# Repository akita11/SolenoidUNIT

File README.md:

# SolenoidUNIT

ソレノイドやDCモータなどの負荷を、Grove端子から最大2個まで制御できます。負荷と電源の接続コネクタの違いで2種類あります。

## SolenoidUNIT

オレンジ色のコネクタ(VH3.96-4p)に、負荷用の電源と負荷を接続します。M5Stackの[BAVGソケット](https://www.switch-science.com/products/7234)を使うと、電源は2.1mmプラグ、負荷はスプリング端子で接続できて便利です。

負荷の電源はオレンジ色のVH3.96コネクタ、またはGrove端子のVDDから選択できます。Grove端子のVDDへの電源供給能力が不足する場合は[TypeC2Grove UNIT](https://www.switch-science.com/products/8453)等を使用してください。

基板形状が「[M5Stack用VH3.96-4ピンユニット[U020]](https://www.switch-science.com/products/4055)」と同一のため、そのケースを使うことができます。

### 使い方

ソレノイドとの接続は、電源供給方法に応じて以下の2通りがあります。制御方法は後述します。

#### ACアダプタ等から供給する場合

ソレノイドの定格電圧が12V等の5Vよりも高い電圧の場合は、ACアダプタ等をオレンジ色コネクタのVS-G間、ソレノイドをA+とA-Bの間に接続します。（M5Stackの[BAVGソケット](https://www.switch-science.com/products/7234)を使うと、電源は2.1mmプラグ、負荷はスプリング端子で接続できて便利です）

#### Grove端子から供給する場合

一般のソレノイドは5Vでは駆動できませんが、5Vで駆動する場合は、電源をGrove端子から供給することができます。
裏面のJP1の、中央-VS(上側)の端子がつながっていますので、カッター等でカットし、中央と反対側の"Grove5V"側を、ハンダを盛るなどしてショートします。これによって、負荷への電源がGrove側の+5Vから供給されます。
ただし、一般にソレノイドは消費電流が多く、マイコン側の+5V電源の供給能力が不足する場合がほとんどです。そのような場合は、[TypeC2Grove UNIT](https://www.switch-science.com/products/8453)を使用して、負荷側の電源をUSB Type-C端子から供給することができます。別途USB-CコネクタのACアダプタ等を接続してください。

#### 2個のソレノイドを制御する場合

必要に応じて、2個のソレノイドを制御することができます。ただし接続がやや複雑ですので、ご注意ください。

- JP2 : VH3.96コネクタの2番ピンの割り当て。「負荷Aのプラス側」（デフォルト）または「負荷Bのマイナス側」。
  - 「負荷Aのプラス側」（デフォルト）の場合（下図(a)）：負荷Aを1番ピン（マイナス側）と2番ピン（プラス側）に接続。負荷は1個のみ(Groveの1番ピンで制御）
  - 「負荷Bのマイナス側の場合」（下図(b)）：負荷A, Bのプラス側はVDD（3番ピン）に接続し、負荷A, Bのマイナス側をそれぞれ1番ピンと2番ピンに接続。負荷は2個（Groveの1番ピン（負荷A）と2番ピン（負荷B）で制御）

## Solenoid5V_UNIT

[タカハの5Vソレノイド](https://www.takaha.co.jp/co/ss/)を接続して制御できます。

基板形状が「[M5Stack用VH3.96-4ピンユニット[U020]](https://www.switch-science.com/products/4055)」と同一のため、そのケースを使うことができます。

2段USBコネクタの上側がソレノイドA（Groveの1番ピンで制御）、下側がソレノイドB（Grovの2番ピンで制御）です。

マイコン（M5Stack等）との接続は以下のように行います。

ただしソレノイドは通電時の消費電流が大きいため、マイコン側の電源供給能力が不足する場合があります。その場合は、[TypeC2Grove UNIT](https://www.switch-science.com/products/8453)を使用して以下のように接続してください。負荷側の電源はUSB Type-C端子から供給することができます。別途USB-CコネクタのACアダプタ等を接続してください。

## マイコン(M5Stack等)からの制御

ソレノイドのの制御は、Grove端子の2本の信号（A/B/VDD/GNDの順）で行います。AまたはBに"1"を与えると負荷がONとなり、"0"でOFFとなります。SolenoidUnitの標準接続（ソレノイド1個）ではA端子のみを使います。

UIFlowでの[使用例](Solenoid5V_test.m5f)（以下）を参考にしてください。（Core2のPortAに接続した場合。A=GPIO32、B=GPIO33）

## Author

Junichi Akita (akita@ifdl.jp, @akita11)

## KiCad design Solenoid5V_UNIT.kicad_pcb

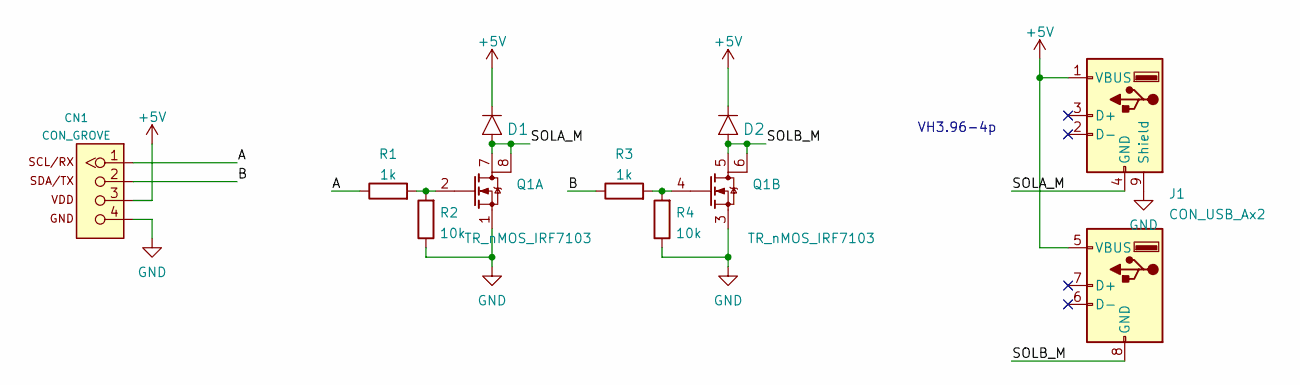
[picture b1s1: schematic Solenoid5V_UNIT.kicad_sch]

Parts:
CN1: CON_GROVE; CON_GROVE_H
D1, D2: DIODE; D_SOD123FL
J1: CON_USB_Ax2; USB_A_Wuerth_61400826021_Horizontal_Stacked
Q1: TR_nMOS_IRF7103; SO-8_3.9x4.9mm_P1.27mm
R1, R3: 1k; R_0603_1608Metric
R2, R4: 10k; R_0603_1608Metric

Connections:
+5V: CN1.3, D1.K, D2.K, J1.1 (VBUS), J1.5 (VBUS)
/A: CN1.1, R1.1
/B: CN1.2, R3.1
/SOLA_M: D1.A, J1.4 (GND), Q1.7 (D), Q1.8 (D2)
/SOLB_M: D2.A, J1.8 (GND), Q1.5 (D), Q1.6 (D2)
GND: CN1.4, J1.9 (Shield), Q1.1 (S), Q1.3 (S), R2.1, R4.1
unnamed: Q1.2 (G), R1.2, R2.2
unnamed: Q1.4 (G), R3.2, R4.2

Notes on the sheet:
VH3.96-4p

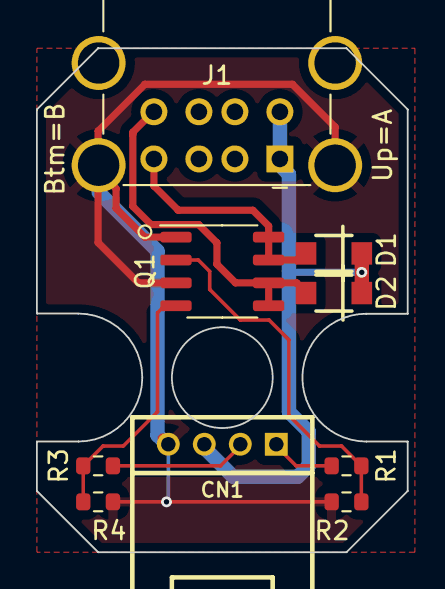
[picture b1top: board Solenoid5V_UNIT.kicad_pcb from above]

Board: 2 copper layers, 20.6 x 28.0 mm, 9 parts (0 on the bottom side), 8 nets.

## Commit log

2022-10-13 draft
2022-11-04 add images
2022-11-07 add image
2022-11-07 image name fix
2022-11-07 image name fix2
2024-03-04 add usage
